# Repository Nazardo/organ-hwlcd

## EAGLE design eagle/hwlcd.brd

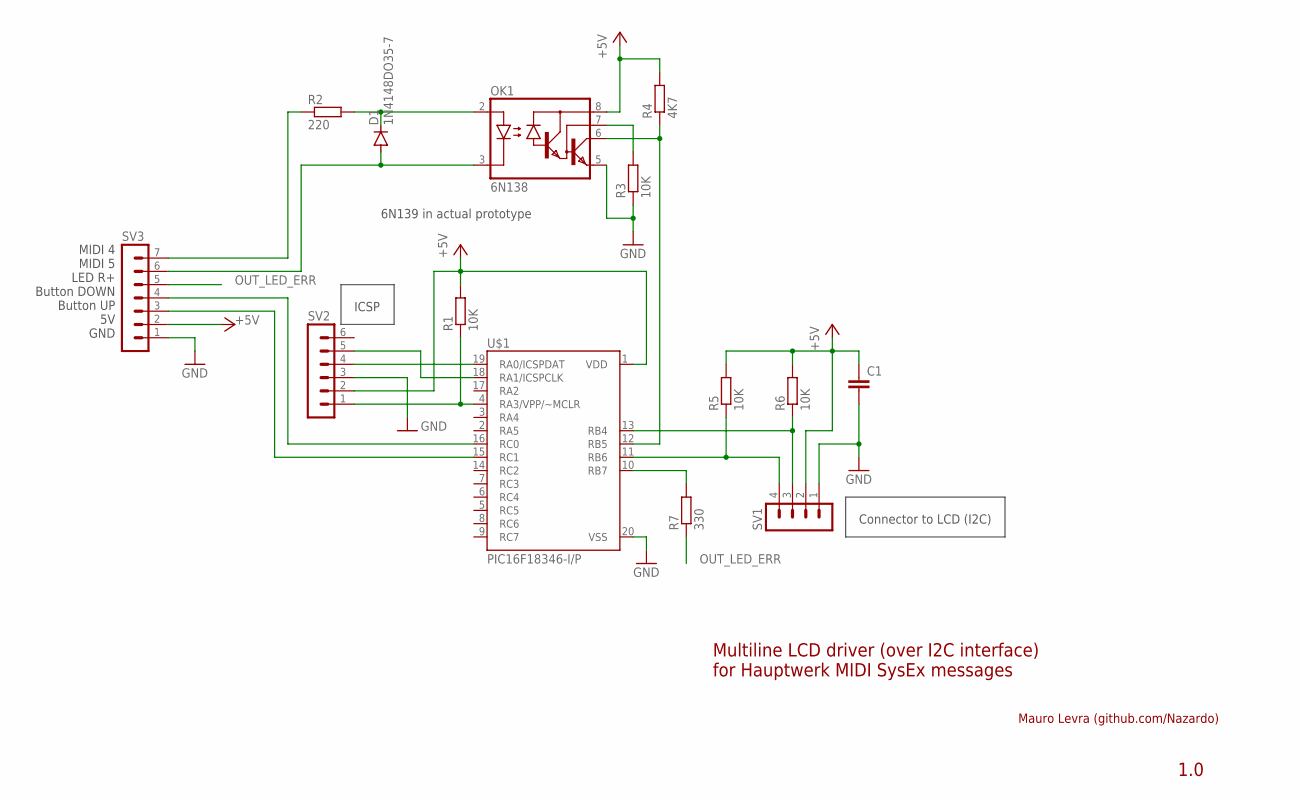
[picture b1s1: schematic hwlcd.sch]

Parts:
C1: C-EU050-025X075; C050-025X075
D1: 1N4148DO35-7; DO35-7
OK1: 6N138; DIL08
R1: 10K; 0204/7
R2: 220; 0204/7
R3: 10K; 0204/5
R4: 4K7; 0204/7
R5, R6: 10K; 0207/2V
R7: 330; 0204V
SV1: MA04-1
SV2: MA06-1
SV3: MA07-1
U$1: PIC16F18346-I/P; DIL20

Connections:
+5V: C1.1, OK1.8 (VCC), R1.2, R4.2, R5.2, R6.2, SV1.2, SV2.2, SV3.2, U$1.1 (VDD)
GND: C1.2, OK1.5 (GND), R3.1, SV1.1, SV2.3, SV3.1, U$1.20 (VSS)
unnamed: SV3.3, U$1.15 (RC1)
unnamed: SV3.4, U$1.16 (RC0)
unnamed: SV2.5, U$1.18 (RA1/ICSPCLK)
unnamed: R1.1, SV2.1, U$1.4 (RA3/VPP/~MCLR)
unnamed: SV2.4, U$1.19 (RA0/ICSPDAT)
unnamed: D1.C, OK1.2 (A), R2.2
unnamed: D1.A, OK1.3 (C), SV3.6
unnamed: R2.1, SV3.7
unnamed: R7.2, U$1.10 (RB7)
unnamed: R6.1, SV1.3, U$1.13 (RB4)
unnamed: OK1.6 (VO), R4.1, U$1.12 (RB5)
unnamed: R5.1, SV1.4, U$1.11 (RB6)
unnamed: OK1.7 (VB), R3.2
OUT_LED_ERR: R7.1, SV3.5

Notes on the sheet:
6N139 in actual prototype
Multiline LCD driver (over I2C interface) for Hauptwerk MIDI SysEx messages
Connector to LCD (I2C)
ICSP
MIDI 4 MIDI 5 LED R+ Button DOWN Button UP 5V GND
1.0
Mauro Levra (github.com/Nazardo)

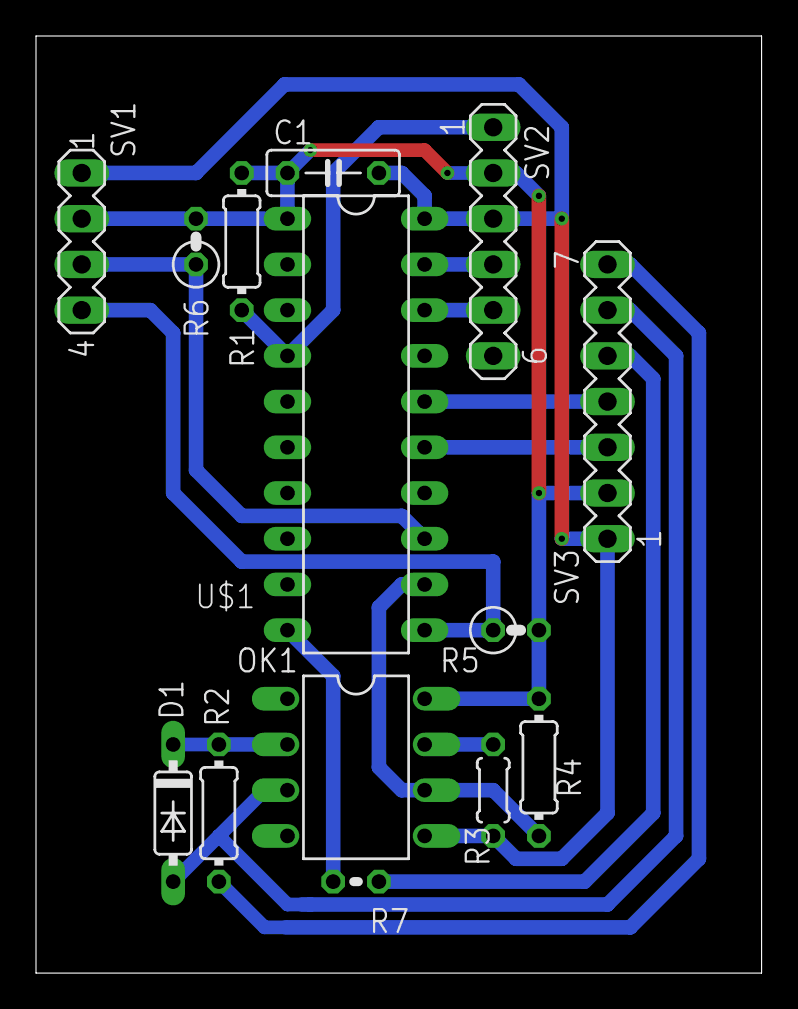
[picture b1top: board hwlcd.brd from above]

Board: 2 copper layers, 40.3 x 52.1 mm, 14 parts (0 on the bottom side), 16 nets.

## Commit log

2019-05-06 Create organ-hwlcd project
2019-05-06 Working LCD messages from Hauptwerk
2019-05-06 Add two buttons for scrollUp/Down
2019-05-06 Add eagle CAD drawing
2019-05-06 Migrate to XC8 2.05, C99
2019-05-15 Init LCD with static text
    A static text is displayed before MIDI messages arrive on the serial
    interface. This is an improvement over an empty LCD screen and also
    displays some information about the project and its release.
